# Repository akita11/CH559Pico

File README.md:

# CH559Pico

[WCH(南京沁恒微电子股份有限公司)](http://wch-ic.com/)の8ビットマイコン[CH559](http://wch-ic.com/products/CH559.html)を使った、RaspberryPi Pico型のマイコンボードです。
主な特徴は以下のとおりです。

- RaspberryPi Pico型
- [ArduinoIDEなどでプログラム開発が可能](https://qiita.com/akita11/items/d7baed4ca3c06e292637)
- USBペリフェラル（キーボードやUSBメモリなど）、USBホストとして動作可能

またRaspberryPi Picoとは、以下のような違いがあります。
- 一部ピンの機能が異なる
- IOピンは基本3.3V（P1.0-7とP4.6/7のみ5V入力OK）
- +3.3V出力の電流供給能力は100mA程度（CH552内蔵レギュレータの性能）
- リセット(RST)は正論理で、"1"でリセット
- +5V端子に、外部電源から+5Vを供給可能（内部にレギュレータはないので、+5Vを超える電圧は不可）

## ピン配置

基板上の"LED"（オレンジ）はP1.5で駆動できます。

※v2ではP4.6とP4.7が空きピンに接続され、水晶発振子を接続できます（裏面に表面実装水晶振動子の接続パッドもあり）

# 訂正

基板上の2個のシルク表示が逆になっているロットがあります。正しくは、RSTスイッチ側のD2が"LED"（オレンジ）、反対側のD1が"POW"（緑、電源インジケータ）です。

## Author

Junichi Akita (@akita11) / akita@ifdl.jp

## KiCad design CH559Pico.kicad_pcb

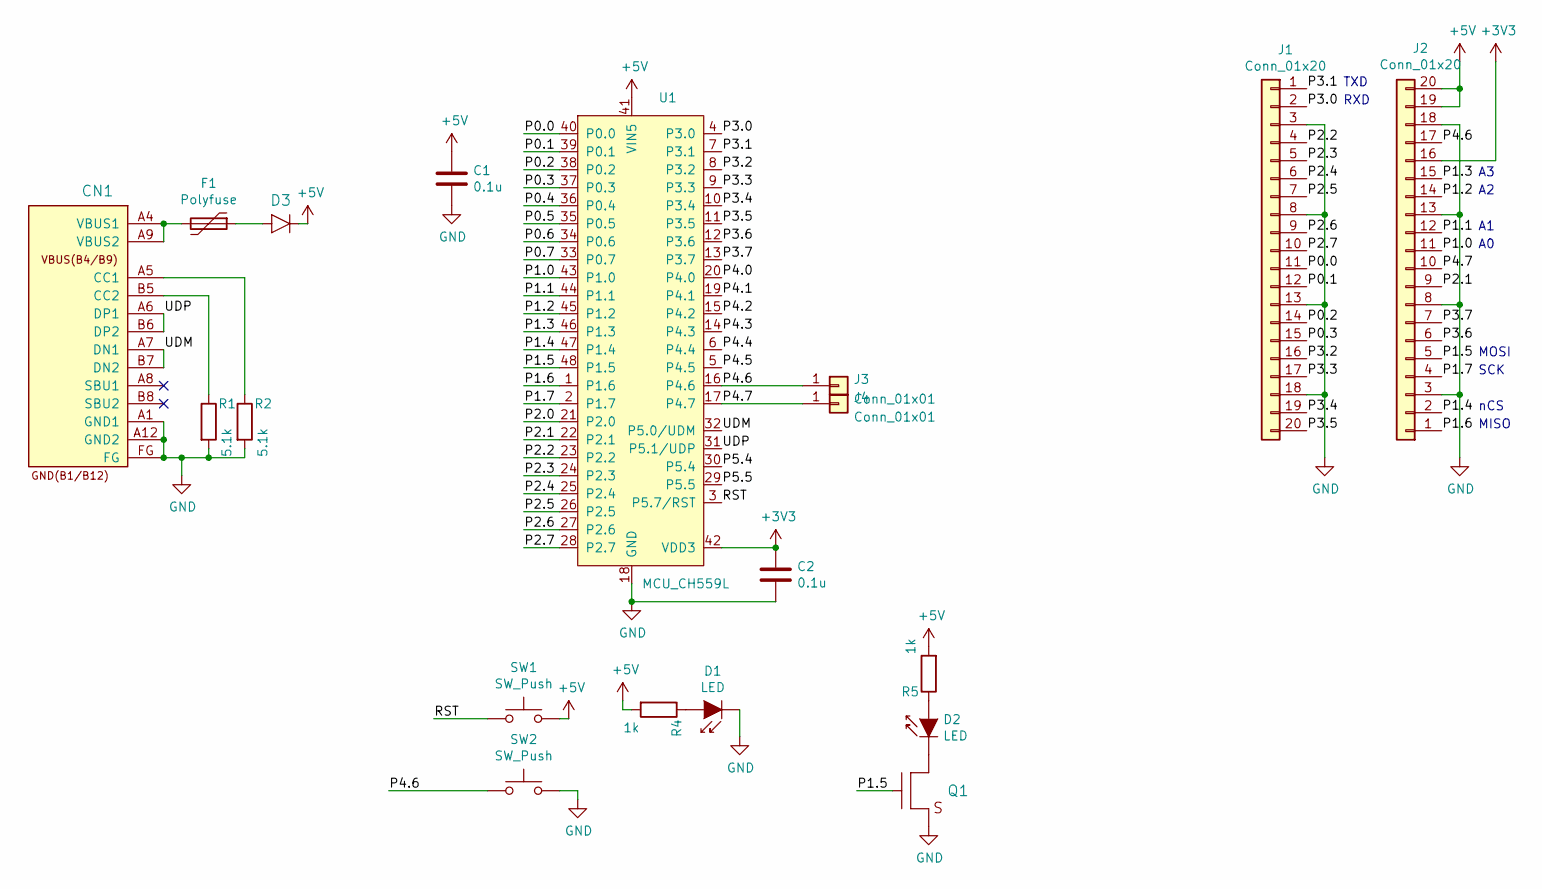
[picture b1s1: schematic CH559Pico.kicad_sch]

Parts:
C1, C2: 0.1u; C_0603_1608Metric; LCSC C14663
CN1: CON_USB-C-16; USB-C_16P_TH; LCSC C165948
D1: LED; LED_0603_1608Metric; LCSC C165982
D2: LED; LED_0603_1608Metric; LCSC C138546
D3: DIODE; D_SOD123FL; LCSC C190475
F1: Polyfuse; R_1210_3225Metric; LCSC C2982267
J1, J2: Conn_01x20; Socker2.54mm_20p_OvalPad
J3, J4: Conn_01x01; Pad_SMD1.6mm
Q1: TR_NMOS_IRLML6344; SOT-23; LCSC C20917
R1, R2: 5.1k; R_0603_1608Metric; LCSC C23186
R4, R5: 1k; R_0603_1608Metric; LCSC C21190
SW1, SW2: SW_Push; SW_Push_SPST_NO_Alps_SKRK; LCSC C2837082
U1: MCU_CH559L; LQFP-48_7x7mm_P0.5mm; LCSC C150548

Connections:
+3V3: C2.1, J2.16, U1.42 (VDD3)
+5V: C1.1, D3.K, J2.19, J2.20, R4.2, R5.2, SW1.2, U1.41 (VIN5)
/P0.0: J1.11, U1.40 (P0.0)
/P0.1: J1.12, U1.39 (P0.1)
/P0.2: J1.14, U1.38 (P0.2)
/P0.3: J1.15, U1.37 (P0.3)
/P0.4: U1.36 (P0.4)
/P0.5: U1.35 (P0.5)
/P0.6: U1.34 (P0.6)
/P0.7: U1.33 (P0.7)
/P1.0: J2.11, U1.43 (P1.0)
/P1.1: J2.12, U1.44 (P1.1)
/P1.2: J2.14, U1.45 (P1.2)
/P1.3: J2.15, U1.46 (P1.3)
/P1.4: J2.2, U1.47 (P1.4)
/P1.5: J2.5, Q1.1 (G), U1.48 (P1.5)
/P1.6: J2.1, U1.1 (P1.6)
/P1.7: J2.4, U1.2 (P1.7)
/P2.0: U1.21 (P2.0)
/P2.1: J2.9, U1.22 (P2.1)
/P2.2: J1.4, U1.23 (P2.2)
/P2.3: J1.5, U1.24 (P2.3)
/P2.4: J1.6, U1.25 (P2.4)
/P2.5: J1.7, U1.26 (P2.5)
/P2.6: J1.9, U1.27 (P2.6)
/P2.7: J1.10, U1.28 (P2.7)
/P3.0: J1.2, U1.4 (P3.0)
/P3.1: J1.1, U1.7 (P3.1)
/P3.2: J1.16, U1.8 (P3.2)
/P3.3: J1.17, U1.9 (P3.3)
/P3.4: J1.19, U1.10 (P3.4)
/P3.5: J1.20, U1.11 (P3.5)
/P3.6: J2.6, U1.12 (P3.6)
/P3.7: J2.7, U1.13 (P3.7)
/P4.0: U1.20 (P4.0)
/P4.1: U1.19 (P4.1)
/P4.2: U1.15 (P4.2)
/P4.3: U1.14 (P4.3)
/P4.4: U1.6 (P4.4)
/P4.5: U1.5 (P4.5)
/P4.6: J2.17, J3.1, SW2.1, U1.16 (P4.6)
/P4.7: J2.10, J4.1, U1.17 (P4.7)
/P5.4: U1.30 (P5.4)
/P5.5: U1.29 (P5.5)
/RST: SW1.1, U1.3 (P5.7/RST)
/UDM: CN1.A7 (DN1), CN1.B7 (DN2), U1.32 (P5.0/UDM)
/UDP: CN1.A6 (DP1), CN1.B6 (DP2), U1.31 (P5.1/UDP)
GND: C1.2, C2.2, CN1.A1 (GND1), CN1.A12 (GND2), CN1.FG, D1.1 (K), J1.3, J1.8, J1.13, J1.18, J2.3, J2.8, J2.13, J2.18, Q1.2 (S), R1.2, R2.2, SW2.2, U1.18 (GND)
unnamed: CN1.A4 (VBUS1), CN1.A9 (VBUS2), F1.2
unnamed: CN1.A5 (CC1), R2.1
unnamed: CN1.B5 (CC2), R1.1
unnamed: D1.2 (A), R4.1
unnamed: D2.1 (K), Q1.3 (D)
unnamed: D2.2 (A), R5.1
unnamed: D3.A, F1.1

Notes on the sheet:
RXD
SCK
MOSI
nCS
MISO
TXD

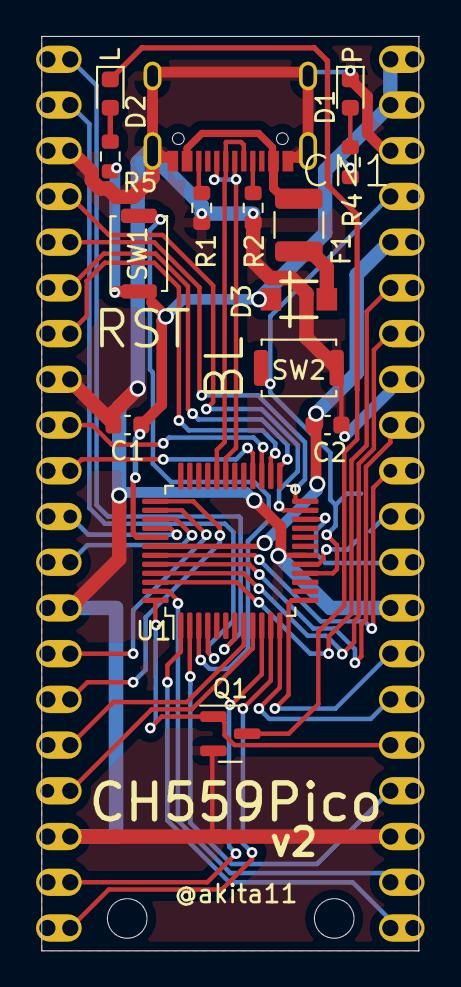
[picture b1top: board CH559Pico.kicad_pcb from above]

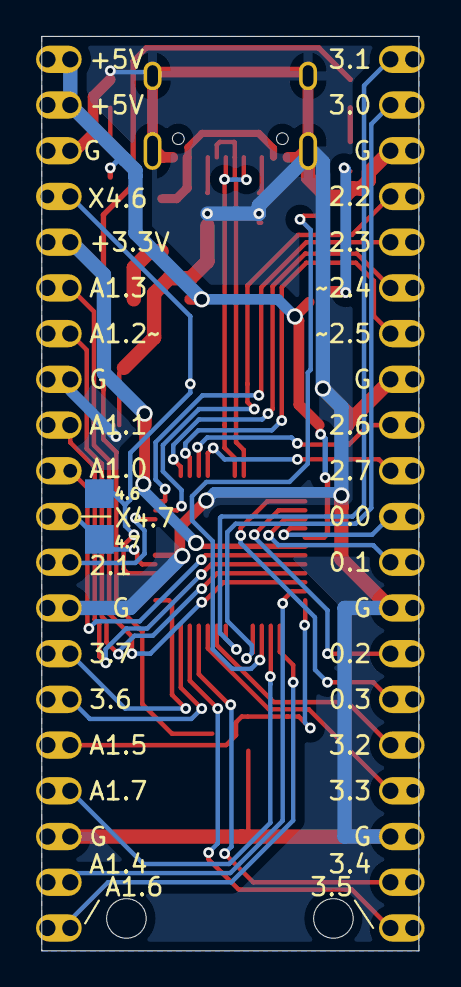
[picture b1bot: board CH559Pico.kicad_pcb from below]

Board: 2 copper layers, 21.0 x 50.8 mm, 19 parts (2 on the bottom side), 42 nets.

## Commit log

2022-01-19 BLピン・シルクの修正
2022-01-19 add pin map
2022-01-20 rename pin map files
2022-01-20 pin map image resize
2022-01-20 外部電源について追記
2022-01-20 rename to CH559Pico
2022-01-26 add image
2022-01-26 modify pin map
2022-01-28 +3.3V出力電流について追記
2022-01-28 add schematic
2022-03-15 new version photo
2022-10-08 update for v2
